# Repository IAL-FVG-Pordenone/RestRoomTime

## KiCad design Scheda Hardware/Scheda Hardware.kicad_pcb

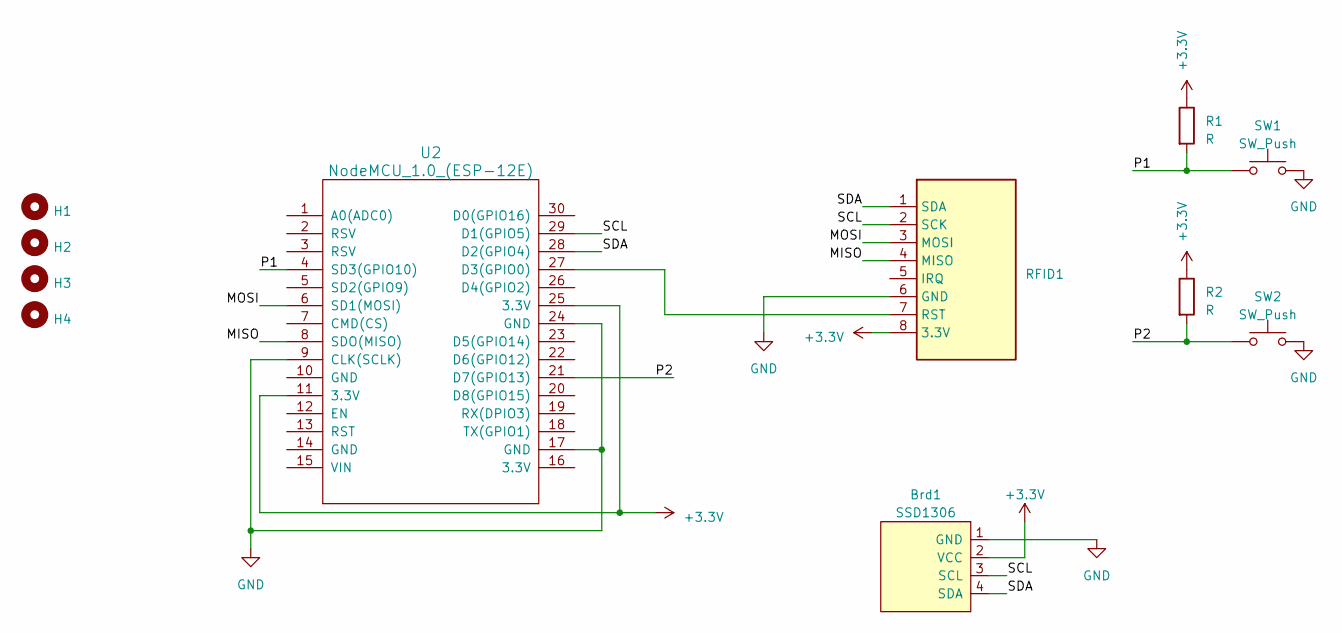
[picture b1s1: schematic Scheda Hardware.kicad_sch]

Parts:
Brd1: SSD1306; 128x64OLED
H1, H2, H3, H4: MountingHole; MountingHole_3.2mm_M3
R1, R2: R; R_Axial_DIN0207_L6.3mm_D2.5mm_P10.16mm_Horizontal
RFID1: RFID-RC522
SW1, SW2: SW_Push; SW_Push_1P1T_NO_6x6mm_H9.5mm
U2: NodeMCU_1.0_(ESP-12E); NodeMCU-LoLinV3

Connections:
+3.3V: Brd1.2 (VCC), R1.1, R2.1, RFID1.8 (3.3V), U2.11 (3.3V), U2.25 (3.3V)
/MISO: RFID1.4 (MISO), U2.8 (SDO(MISO))
/MOSI: RFID1.3 (MOSI), U2.6 (SD1(MOSI))
/P1: R1.2, SW1.1, U2.4 (SD3(GPIO10))
/P2: R2.2, SW2.1, U2.21 (D7(GPIO13))
/SCL: Brd1.3 (SCL), RFID1.2 (SCK), U2.29 (D1(GPIO5))
/SDA: Brd1.4 (SDA), RFID1.1 (SDA), U2.28 (D2(GPIO4))
GND: Brd1.1 (GND), RFID1.6 (GND), SW1.2, SW2.2, U2.9 (CLK(SCLK)), U2.17 (GND), U2.24 (GND)
unnamed: RFID1.7 (RST), U2.27 (D3(GPIO0))

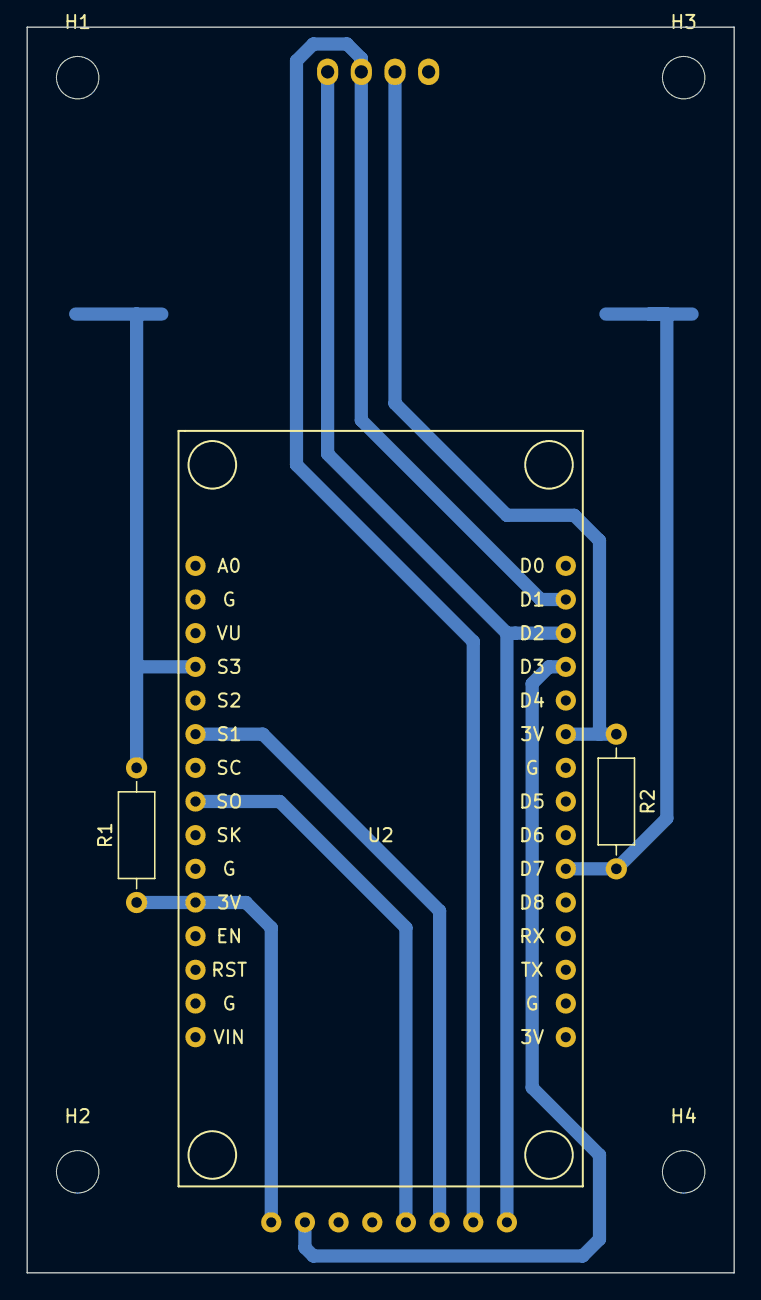
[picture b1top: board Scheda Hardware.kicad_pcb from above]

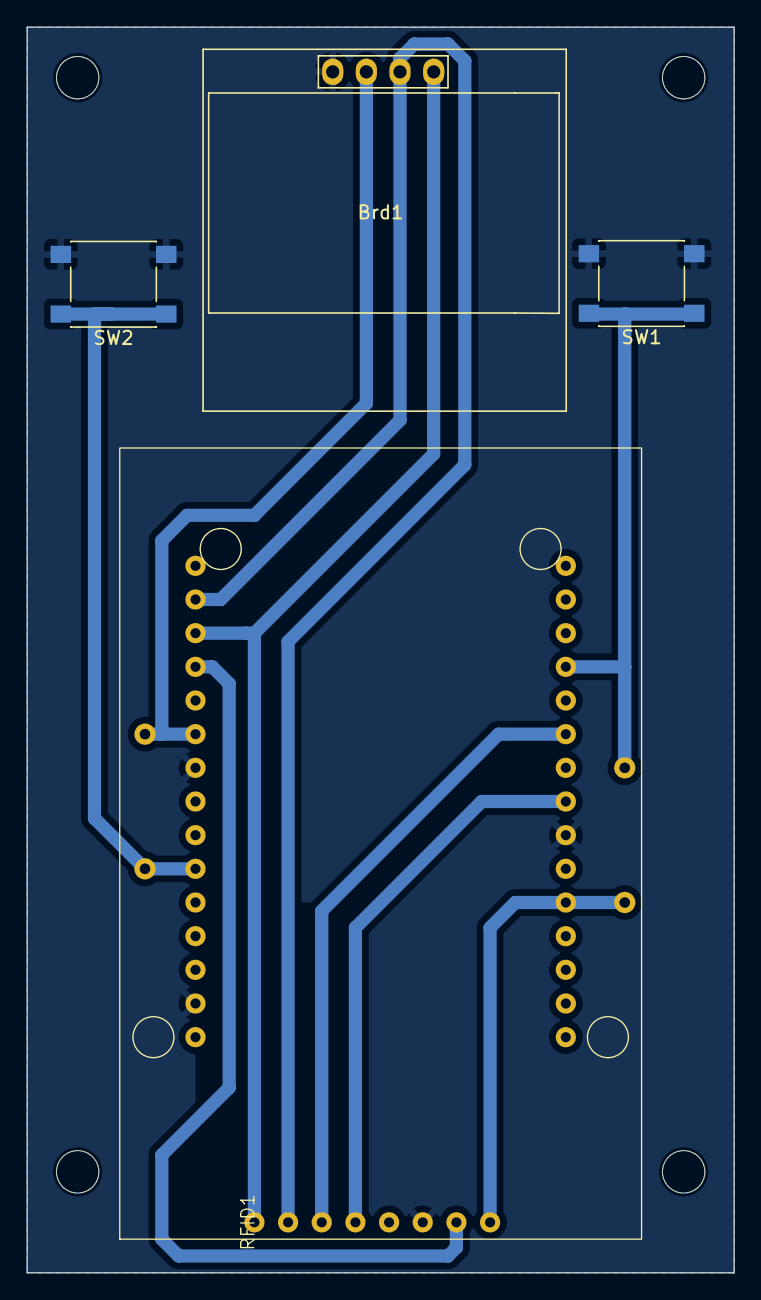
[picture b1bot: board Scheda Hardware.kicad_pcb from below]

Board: 2 copper layers, 53.3 x 94.0 mm, 11 parts (4 on the bottom side), 9 nets.

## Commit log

2023-04-12 Schema
2023-04-17 updateX
2023-04-21 V1.0
